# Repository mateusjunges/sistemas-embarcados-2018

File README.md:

<h1>Sistemas Embarcados 2018</h1>
<hr>
<p>Repositório com o conteúdo das aulas de sistemas embarcados do curso de Engenharia de Computação, da Universidade Estadual de Ponta Grossa - UEPG</p>

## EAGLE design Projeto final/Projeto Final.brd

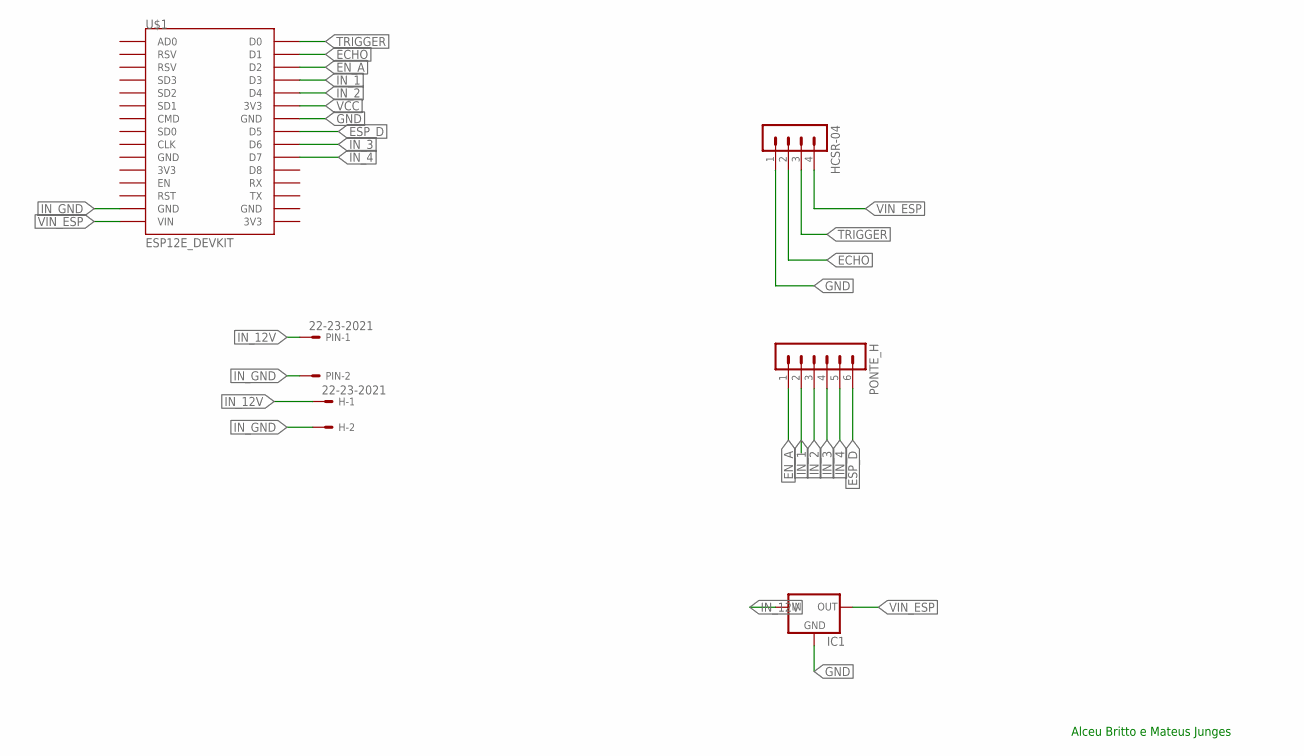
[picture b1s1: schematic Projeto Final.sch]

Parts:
H: 22-23-2021
HCSR-04: MA04-1
IC1: 78XXL
PIN: 22-23-2021
PONTE_H: MA06-1
U$1: ESP12E_DEVKIT

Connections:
ECHO: HCSR-04.2, U$1.D1
EN_A: PONTE_H.1, U$1.D2
ESP_D: PONTE_H.6, U$1.D5
GND: HCSR-04.1, IC1.GND, U$1.GND@2 (GND)
IN_1: PONTE_H.2, U$1.D3
IN_2: PONTE_H.3, U$1.D4
IN_3: PONTE_H.4, U$1.D6
IN_4: PONTE_H.5, U$1.D7
IN_12V: H.1, IC1.IN, PIN.1
IN_GND: H.2, PIN.2, U$1.GND@1 (GND)
TRIGGER: HCSR-04.3, U$1.D0
VCC: U$1.3V3@1 (3V3)
VIN_ESP: HCSR-04.4, IC1.OUT, U$1.VIN

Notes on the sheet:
Alceu Britto e Mateus Junges

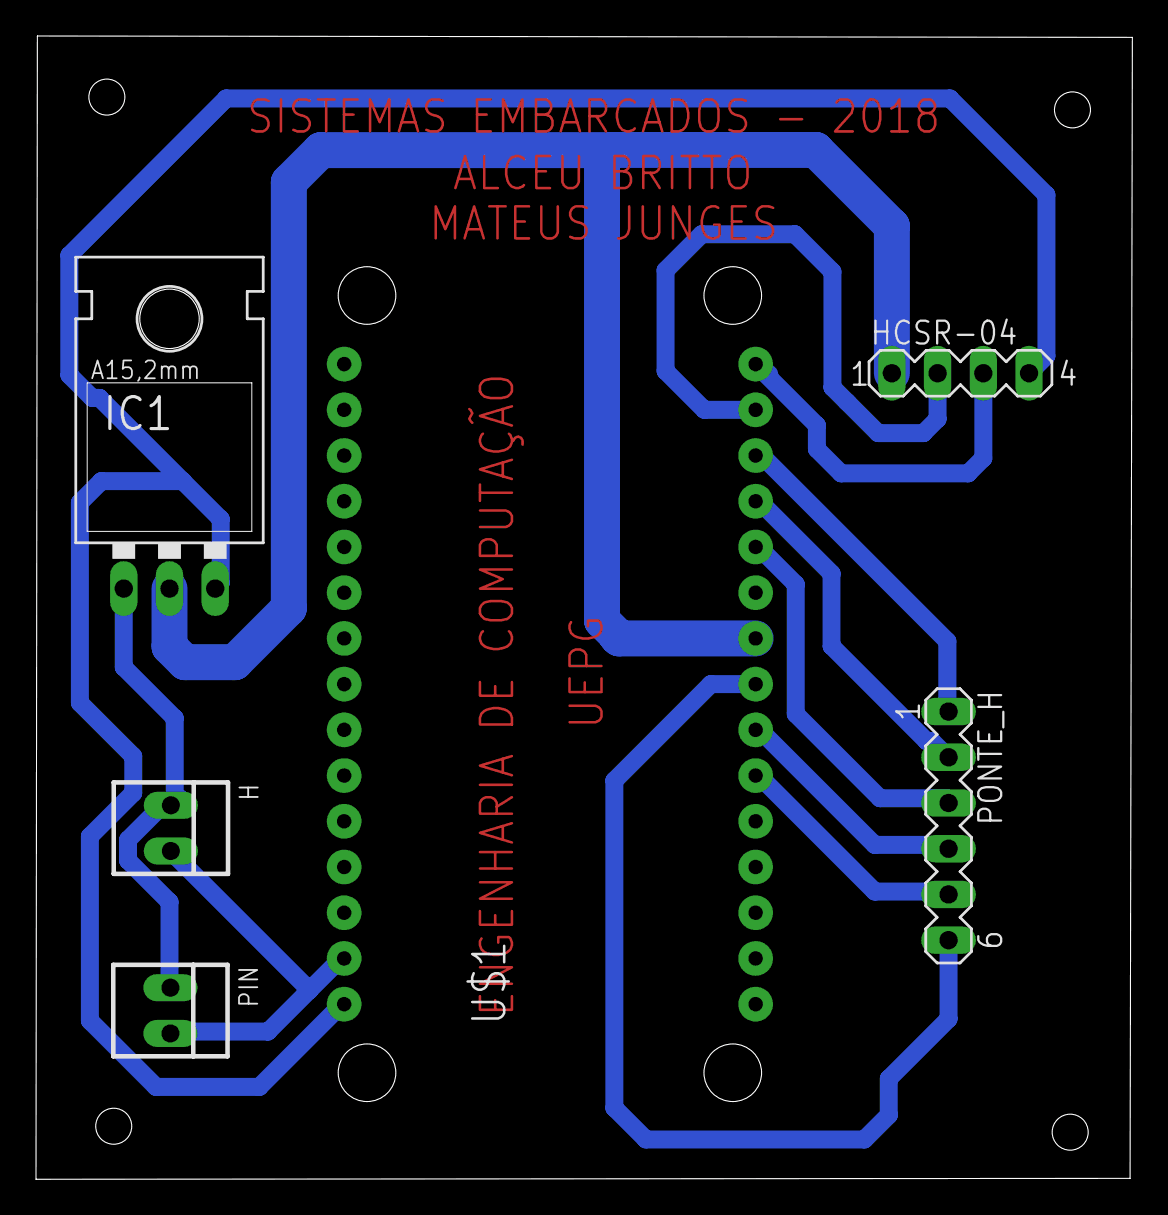
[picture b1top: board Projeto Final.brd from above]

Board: 2 copper layers, 60.9 x 63.5 mm, 6 parts (0 on the bottom side), 12 nets.

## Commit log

2018-08-14 Aulas
2018-08-16 Correções controle IO e add aula UART Bluetooth
2018-08-16 add README
2018-08-16 Pinagem ESP8266
2018-08-16 Add arquivos .sch
2018-08-16 Create LICENSE
2018-08-16 organização dos diretórios
2018-08-16 Atividade 1
2018-08-16 Esquemas de ligação dos circuitos
2018-08-21 Datasheet hc06
2018-08-21 Atividade 2
2018-08-21 Atividade 02
2018-08-21 Eagle libraries
2018-08-23 Web server ESP8266
2018-08-28 Web server e web client esp 8266
2018-09-04 04/09
2018-09-06 Display com sensor
2018-09-07 Display + termometro + LDR
2018-09-09 Display, termometro e LDR com i2c
2018-09-10 dispositivos i2c
2018-09-10 Correção
2018-09-10 Esquemático - Dispositivos I2C
2018-09-26 Servo motores e mux
2018-10-01 Atividade controle motor com teclado numérico
2018-10-30 MQTT
2018-10-30 Atividade MQTT
2018-11-01 Comunicação sensor infra vermelho e protocolo MQTT
2018-11-01 IR sensor
2018-11-20 Controle remoto - TV samsung
2018-11-20 Controle remoto
2018-11-22 Controler remoto
2018-11-25 Projeto final
2018-12-09 Arquivos aulas
2018-12-09 Arquivos projeto final
